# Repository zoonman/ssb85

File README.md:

# ssb85
My work-in-progress hamradio transceiver.

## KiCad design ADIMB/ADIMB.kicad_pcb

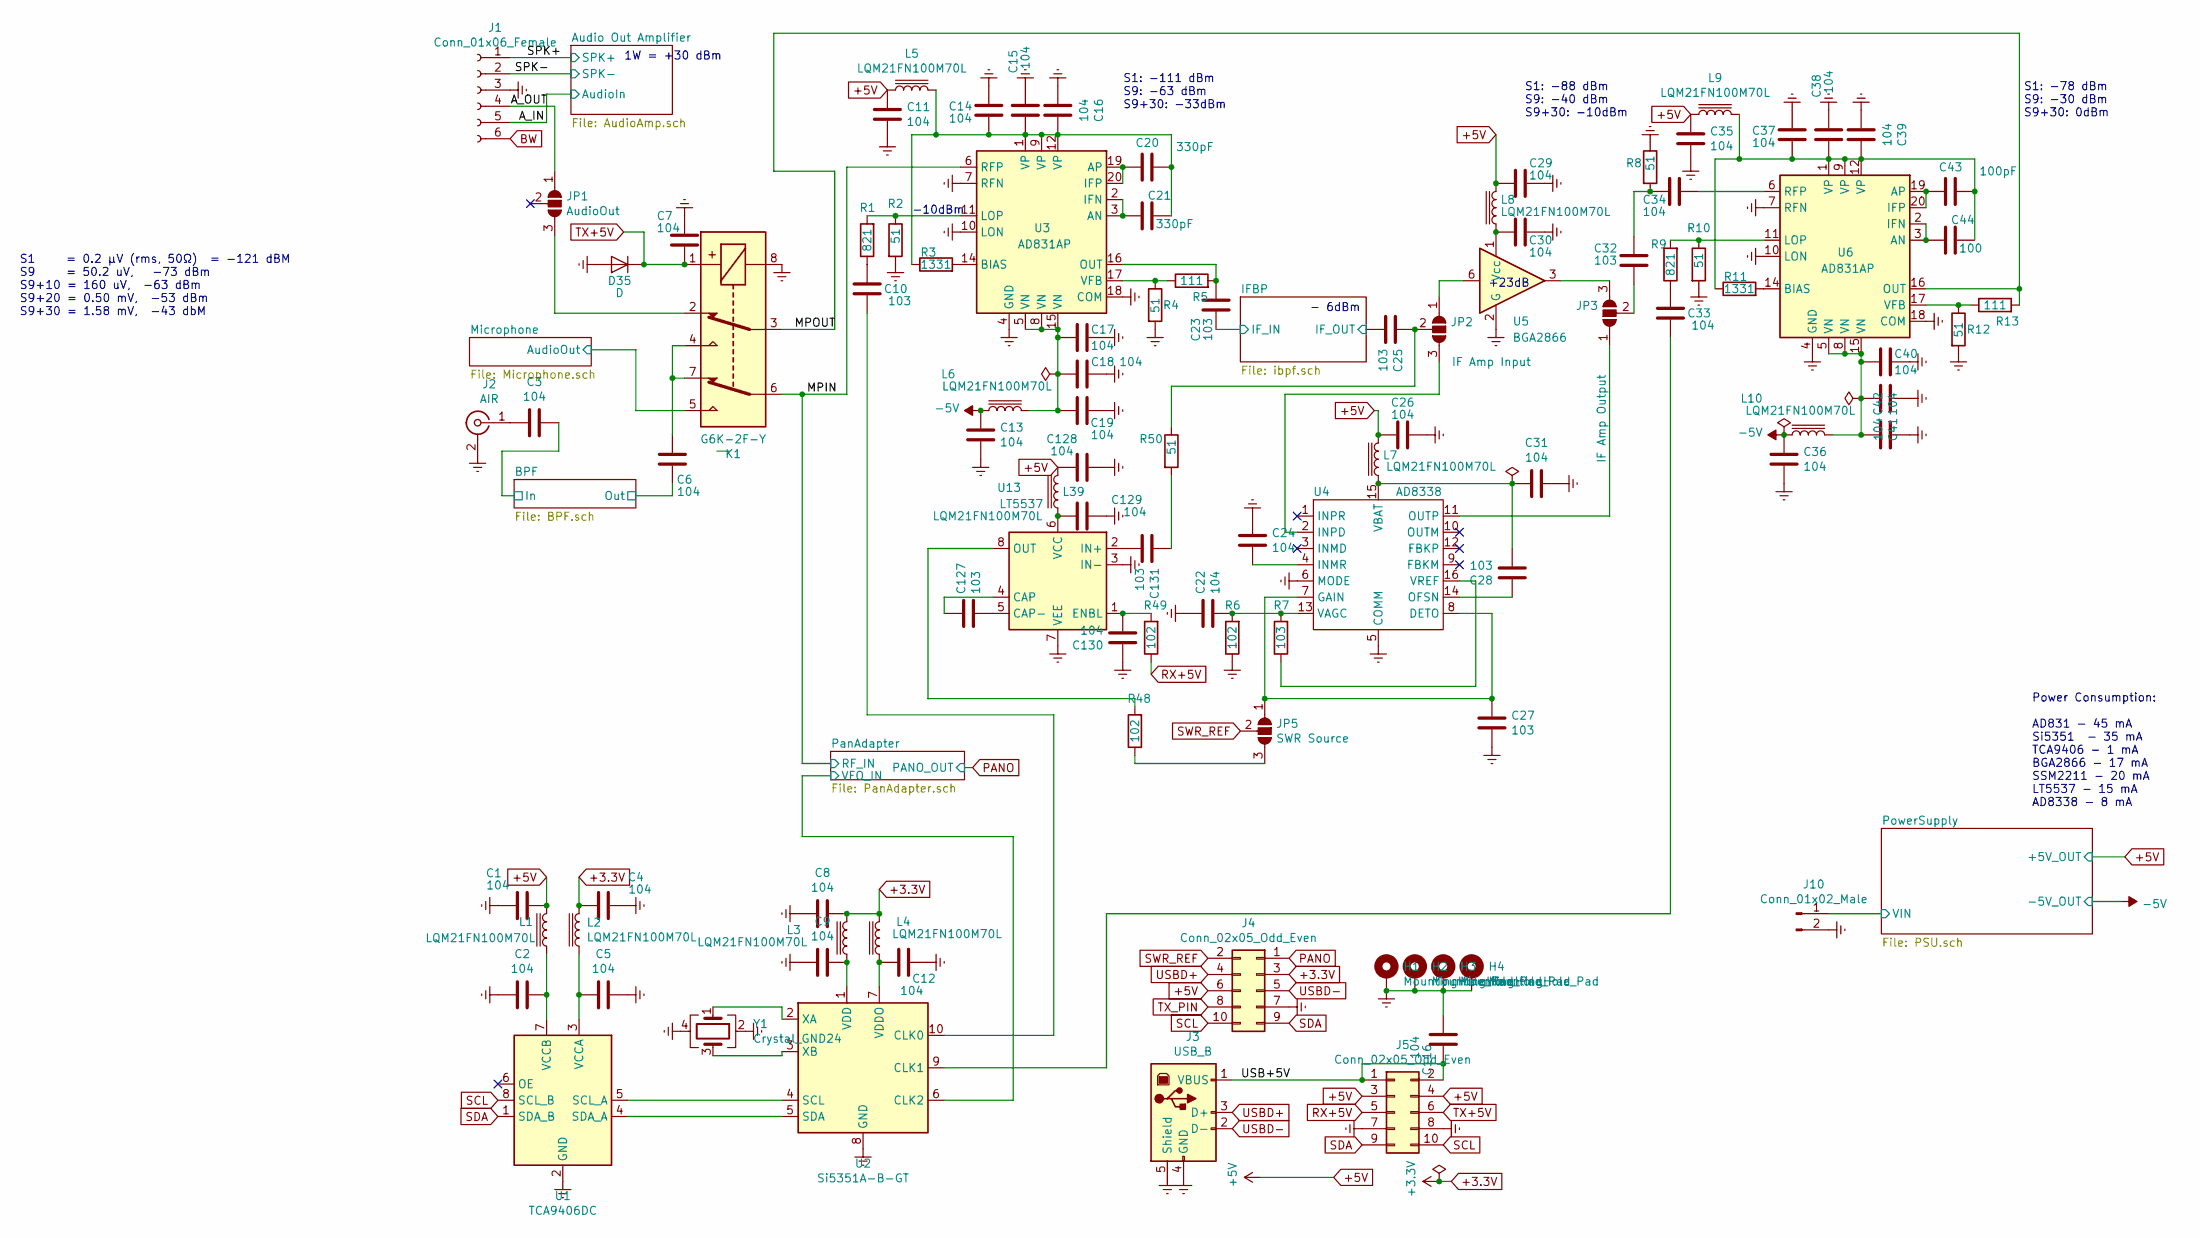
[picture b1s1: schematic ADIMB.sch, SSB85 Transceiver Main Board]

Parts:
C1, C2, C3, C4, C5, C6, C7, C8, C9, C11, C12, C13, C14, C15, C16, C17, C18, C19, C22, C24, C26, C29, C30, C31, C33, C34, C35, C36, C37, C38, C39, C40, C41, C42, C116, C128, C129, C130: 104; C_0805_2012Metric
C10, C23, C25, C27, C28, C32, C127, C131: 103; C_0805_2012Metric
C20, C21: 330pF; C_0805_2012Metric
C43: 100pF; C_0805_2012Metric
C44: 100; C_0805_2012Metric
D35: D; D_SOD-123
H1, H2, H3, H4: MountingHole_Pad; MountingHole_3.2mm_M3_Pad_Via
J1: Conn_01x06_Female; PinSocket_1x06_P2.54mm_Horizontal
J2: AIR; SMA_Amphenol_901-144_Vertical
J3: USB_B; USB_B_OST_USB-B1HSxx_Horizontal
J4: Conn_02x05_Odd_Even; PinSocket_2x05_P2.54mm_Horizontal
J5: Conn_02x05_Odd_Even; PinSocket_2x05_P2.54mm_Vertical
J10: Conn_01x02_Male; PinHeader_1x02_P2.54mm_Vertical
JP1: AudioOut; SolderJumper-3_P1.3mm_Open_RoundedPad1.0x1.5mm
JP2: IF Amp Input; SolderJumper-3_P1.3mm_Open_RoundedPad1.0x1.5mm
JP3: IF Amp Output; SolderJumper-3_P1.3mm_Open_RoundedPad1.0x1.5mm
JP5: SWR Source; SolderJumper-3_P1.3mm_Open_RoundedPad1.0x1.5mm
K1: G6K-2F-Y; Relay_DPDT_Omron_G6K-2F-Y
L1, L2, L3, L4, L5, L6, L7, L8, L9, L10, L39: LQM21FN100M70L; L_0805_2012Metric
R1, R9: 821; R_0805_2012Metric
R2, R4, R8, R10, R12, R50: 51; R_0805_2012Metric
R3, R11: 1331; R_0805_2012Metric
R5, R13: 111; R_0805_2012Metric
R6, R48, R49: 102; R_0805_2012Metric
R7: 103; R_0805_2012Metric
U1: TCA9406DC; VSSOP-8_2.3x2mm_P0.5mm
U2: Si5351A-B-GT; MSOP-10_3x3mm_P0.5mm
U3, U6: AD831AP; PLCC-20
U4: AD8338; LFCSP-16-1EP_3x3mm_P0.5mm_EP1.7x1.7mm
U5: BGA2866; SOT-363_SC-70-6
U13: LT5537; DFN-8-1EP_2x3mm_P0.5mm_EP0.61x2.2mm
Y1: Crystal_GND24; Crystal_SMD_Abracon_ABM8G-4Pin_3.2x2.5mm

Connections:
+3.3V: C4.2, C8.1, J4.3, L2.2, L3.2, L4.2
+5V: C1.1, C11.1, C26.2, C29.2, C35.1, C128.2, J4.6, J5.3, J5.4, L1.2, L5.1, L7.2, L8.2, L9.1, L39.2; also elsewhere on the board
-5V: C13.1, C36.1, L6.1, L10.1; also elsewhere on the board
/A_IN: J1.5; also elsewhere on the board
/A_OUT: J1.4, JP1.1 (A)
/BPF/In: C3.1; also elsewhere on the board
/BPF/Out: C6.1; also elsewhere on the board
/IFBP/IF_IN: C23.1; also elsewhere on the board
/IFBP/IF_OUT: C25.2; also elsewhere on the board
/MPIN: K1.6, U3.6 (RFP); also elsewhere on the board
/MPOUT: K1.3, R13.2, U6.16 (OUT)
/Microphone/AudioOut: K1.5; also elsewhere on the board
/PanAdapter/VFO_IN: U2.6 (CLK2); also elsewhere on the board
/PowerSupply/VIN: J10.1; also elsewhere on the board
/SPK+: J1.1; also elsewhere on the board
/SPK-: J1.2; also elsewhere on the board
/USB+5V: C116.1, J3.1 (VBUS), J5.1, J5.2
BW: J1.6; also elsewhere on the board
Earth: C1.2, C2.2, C4.1, C5.1, C7.1, C8.2, C9.2, C11.2, C12.1, C13.2, C14.2, C15.2, C16.2, C17.1, C18.1, C19.2, C22.1, C24.1, C26.1, C27.2, C29.1, C30.1, C31.1, C35.2, C36.2, C37.2, C38.2, C39.2, C40.1, C41.1, C42.2, C116.2, C128.1, C129.1, C130.1, D35.2 (A), H1.1, H2.1, H3.1, H4.1, J1.3, J2.2 (Ext), J3.4 (GND), J3.5 (Shield), J4.7, J5.7, J5.8, J10.2, K1.8, R2.2, R4.2, R6.1, R8.1, R10.2, R12.2, U1.2 (GND), U2.8 (GND), U3.4 (GND), U3.7 (RFN), U3.10 (LON), U3.13 (GND), U3.18 (COM), U4.5 (COMM), U4.6 (MODE), U4.17 (EPAD), U5.2 (G), U5.4 (G), U5.5 (G), U6.4 (GND), U6.7 (RFN), U6.10 (LON), U6.13 (GND), U6.18 (COM), U13.3 (IN-), U13.7 (VEE), U13.9 (PAD), Y1.2, Y1.4; also elsewhere on the board
unnamed: C2.1, L1.1, U1.7 (VCCB)
unnamed: C3.2, J2.1 (In)
unnamed: C5.2, L2.1, U1.3 (VCCA)
unnamed: C6.2, K1.4, K1.7
unnamed: C9.1, L3.1, U2.1 (VDD)
unnamed: C10.1, R1.1
unnamed: C10.2, U2.10 (CLK0)
unnamed: C12.2, L4.1, U2.7 (VDDO)
unnamed: C14.1, C15.1, C16.1, C20.1, C21.1, L5.2, R3.1, U3.1 (VP), U3.9 (VP), U3.12 (VP)
unnamed: C17.2, C18.2, C19.1, L6.2, U3.5 (VN), U3.8 (VN), U3.15 (VN)
unnamed: C20.2, U3.19 (AP), U3.20 (IFP)
unnamed: C21.2, U3.2 (IFN), U3.3 (AN)
unnamed: C22.2, R6.2, R7.2, U4.13 (VAGC)
unnamed: C23.2, R5.2, U3.16 (OUT)
unnamed: C24.2, U4.4 (INMR)
unnamed: C25.1, JP2.2 (C), R50.1
unnamed: C27.1, JP5.1 (A), U4.7 (GAIN), U4.8 (DETO)
unnamed: C28.1, U4.14 (OFSN)
unnamed: C28.2, C31.2, L7.1, U4.15 (VBAT)
unnamed: C30.2, L8.1, U5.1 (Vcc)
unnamed: C32.1, JP3.2 (C)
unnamed: C32.2, C34.2, R8.2
unnamed: C33.1, R9.1
unnamed: C33.2, U2.9 (CLK1)
unnamed: C34.1, U6.6 (RFP)
unnamed: C37.1, C38.1, C39.1, C43.1, C44.1, L9.2, R11.1, U6.1 (VP), U6.9 (VP), U6.12 (VP)
unnamed: C40.2, C41.2, C42.1, L10.2, U6.5 (VN), U6.8 (VN), U6.15 (VN)
unnamed: C43.2, U6.19 (AP), U6.20 (IFP)
unnamed: C44.2, U6.2 (IFN), U6.3 (AN)
unnamed: C127.1, U13.4 (CAP)
unnamed: C127.2, U13.5 (CAP-)
unnamed: C129.2, L39.1, U13.6 (VCC)
unnamed: C130.2, R49.2, U13.1 (ENBL)
unnamed: C131.1, R50.2
unnamed: C131.2, U13.2 (IN+)
unnamed: JP1.3 (B), K1.2
unnamed: JP2.1 (A), U5.6
unnamed: JP2.3 (B), U4.2 (INPD)
unnamed: JP3.1 (A), U4.11 (OUTP)
unnamed: JP3.3 (B), U5.3
unnamed: JP5.3 (B), R48.1
unnamed: R1.2, R2.1, U3.11 (LOP)
unnamed: R3.2, U3.14 (BIAS)
unnamed: R4.1, R5.1, U3.17 (VFB)
unnamed: R7.1, U4.16 (VREF)
unnamed: R9.2, R10.1, U6.11 (LOP)
unnamed: R11.2, U6.14 (BIAS)
unnamed: R12.1, R13.1, U6.17 (VFB)
unnamed: R48.2, U13.8 (OUT)
unnamed: U1.4 (SDA_A), U2.5 (SDA)
unnamed: U1.5 (SCL_A), U2.4 (SCL)
unnamed: U2.2 (XA), Y1.1
unnamed: U2.3 (XB), Y1.3
PANO: J4.1; also elsewhere on the board
RX+5V: J5.5, R49.1; also elsewhere on the board
SCL: J4.10, J5.10, U1.8 (SCL_B); also elsewhere on the board
SDA: J4.9, J5.9, U1.1 (SDA_B); also elsewhere on the board
SWR_REF: J4.2, JP5.2 (C)
TX+5V: C7.2, D35.1 (K), J5.6, K1.1; also elsewhere on the board
TX_PIN: J4.8; also elsewhere on the board
USBD+: J3.3 (D+), J4.4
USBD-: J3.2 (D-), J4.5

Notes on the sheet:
S1 = 0.2 μV (rms, 50Ω) = -121 dBM S9 = 50.2 uV, -73 dBm S9+10 = 160 uV, -63 dBm S9+20 = 0.50 mV, -53 dBm S9+30 = 1.58 mV, -43 dbM
1W = +30 dBm
S1: -111 dBm S9: -63 dBm S9+30: -33dBm
-10dBm
- 6dBm
+23dB
S1: -88 dBm S9: -40 dBm S9+30: -10dBm
S1: -78 dBm S9: -30 dBm S9+30: 0dBm
Power Consumption: AD831 - 45 mA Si5351 - 35 mA TCA9406 - 1 mA BGA2866 - 17 mA SSM2211 - 20 mA LT5537 - 15 mA AD8338 - 8 mA

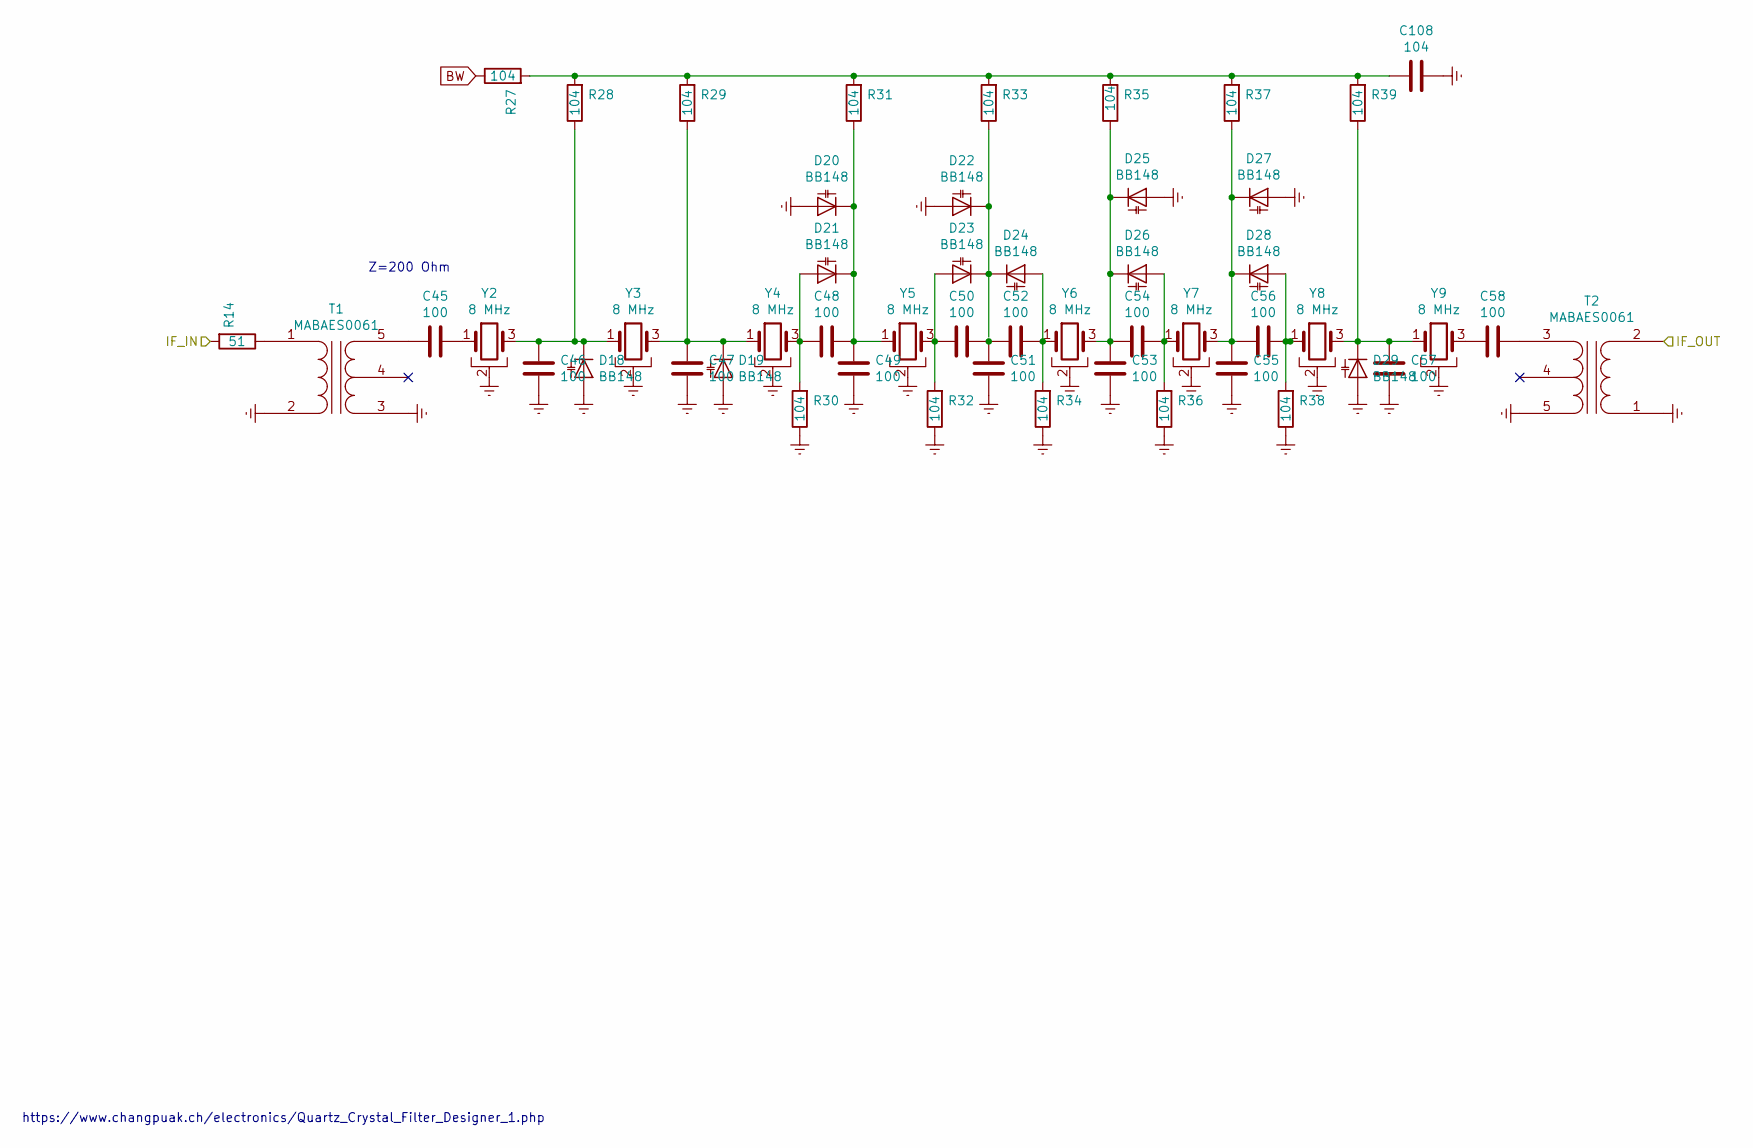
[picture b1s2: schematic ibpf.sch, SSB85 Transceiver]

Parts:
C45, C46, C47, C48, C49, C50, C51, C52, C53, C54, C55, C56, C57, C58: 100; C_0805_2012Metric
C108: 104; C_0805_2012Metric
D18: BB148; D_SOD-323
D19, D20, D21, D22, D23, D24, D25, D26, D27, D28, D29: BB148; D_SOD-323_HandSoldering
R14: 51; R_0805_2012Metric
R27, R28, R29, R30, R31, R32, R33, R34, R35, R36, R37, R38, R39: 104; R_0805_2012Metric
T1, T2: MABAES0061; Transformer_MACOM_SM-22
Y2, Y3, Y4, Y5, Y6, Y7, Y8, Y9: 8 MHz; Crystal_HC49-U-3Pin_Vertical

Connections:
/IFBP/IF_IN: R14.2; also elsewhere on the board
/IFBP/IF_OUT: T2.2 (AB); also elsewhere on the board
BW: R27.1; also elsewhere on the board
Earth: C46.1, C47.1, C49.1, C51.1, C53.1, C55.1, C57.1, C108.1, D18.2 (A), D19.2 (A), D20.2 (A), D22.2 (A), D25.2 (A), D27.2 (A), D29.2 (A), R30.1, R32.1, R34.1, R36.1, R38.1, T1.2 (AB), T1.3 (SA), T2.1 (AA), T2.5 (SB), Y2.2, Y3.2, Y4.2, Y5.2, Y6.2, Y7.2, Y8.2, Y9.2; also elsewhere on the board
unnamed: C45.1, Y2.1
unnamed: C45.2, T1.5 (SB)
unnamed: C46.2, D18.1 (K), R28.1, Y2.3, Y3.1
unnamed: C47.2, D19.1 (K), R29.1, Y3.3, Y4.1
unnamed: C48.1, C49.2, D20.1 (K), D21.1 (K), R31.1, Y5.1
unnamed: C48.2, D21.2 (A), R30.2, Y4.3
unnamed: C50.1, C51.2, C52.2
unnamed: C50.2, D23.2 (A), R32.2, Y5.3
unnamed: C52.1, D24.2 (A), R34.2, Y6.1
unnamed: C53.2, C54.2, D25.1 (K), D26.1 (K), R35.1, Y6.3
unnamed: C54.1, D26.2 (A), R36.2, Y7.1
unnamed: C55.2, C56.2, D27.1 (K), D28.1 (K), R37.1, Y7.3
unnamed: C56.1, D28.2 (A), R38.2, Y8.1
unnamed: C57.2, D29.1 (K), R39.1, Y8.3, Y9.1
unnamed: C58.1, T2.3 (SA)
unnamed: C58.2, Y9.3
unnamed: C108.2, R27.2, R28.2, R29.2, R31.2, R33.2, R35.2, R37.2, R39.2
unnamed: D22.1 (K), D23.1 (K), D24.1 (K), R33.1
unnamed: R14.1, T1.1 (AA)

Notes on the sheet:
Z=200 Ohm
https://www.changpuak.ch/electronics/Quartz_Crystal_Filter_Designer_1.php

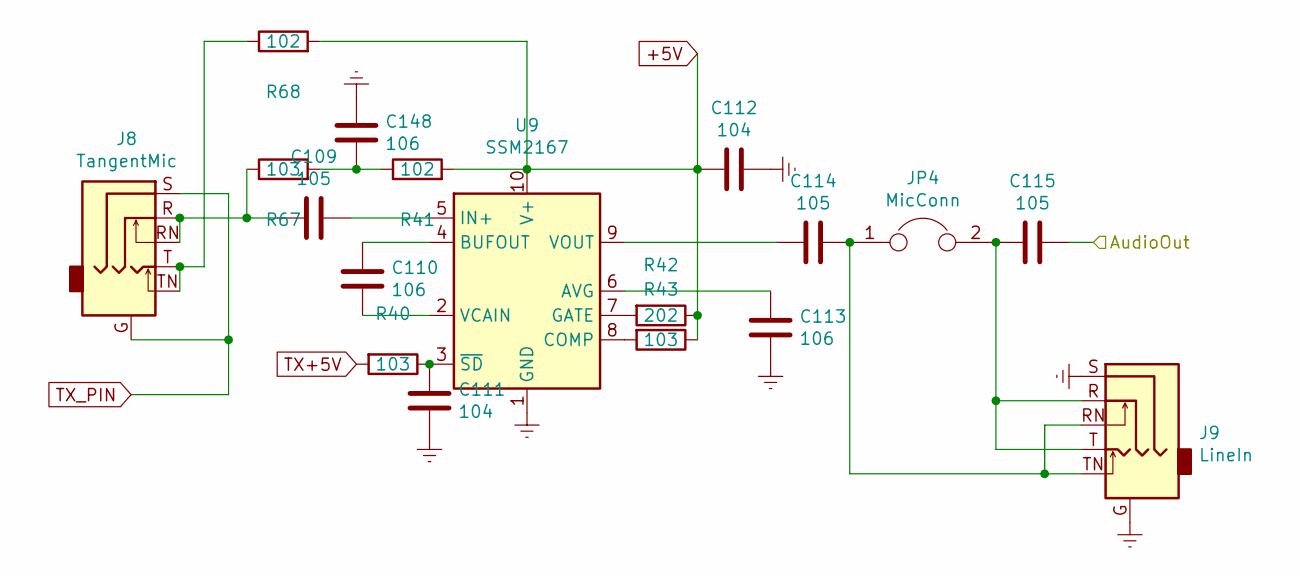
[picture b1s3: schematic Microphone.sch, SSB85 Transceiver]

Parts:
C109, C114, C115: 105; C_0805_2012Metric
C110, C113, C148: 106; C_0805_2012Metric
C111, C112: 104; C_0805_2012Metric
J8: TangentMic; Jack_3.5mm_PJ342_Horizontal2
J9: LineIn; Jack_3.5mm_PJ342_Horizontal2
JP4: MicConn; SolderJumper-2_P1.3mm_Open_RoundedPad1.0x1.5mm
R40, R43, R67: 103; R_0805_2012Metric
R41, R68: 102; R_0805_2012Metric
R42: 202; R_0805_2012Metric
U9: SSM2167; MSOP-10_3x3mm_P0.5mm

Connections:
+5V: C112.1, R41.2, R42.1, R43.1, R68.2, U9.10 (V+); also elsewhere on the board
/Microphone/AudioOut: C115.1; also elsewhere on the board
Earth: C111.1, C112.2, C113.2, C148.1, J9.G, J9.S, U9.1 (GND); also elsewhere on the board
unnamed: C109.1, U9.5 (IN+)
unnamed: C109.2, J8.R, J8.RN, R67.1
unnamed: C110.1, U9.4 (BUFOUT)
unnamed: C110.2, U9.2 (VCAIN)
unnamed: C111.2, R40.1, U9.3 (~SD)
unnamed: C113.1, U9.6 (AVG)
unnamed: C114.1, J9.RN, J9.TN, JP4.1
unnamed: C114.2, U9.9 (VOUT)
unnamed: C115.2, J9.R, J9.T, JP4.2
unnamed: C148.2, R41.1, R67.2
unnamed: J8.T, J8.TN, R68.1
unnamed: R42.2, U9.7 (GATE)
unnamed: R43.2, U9.8 (COMP)
TX+5V: R40.2; also elsewhere on the board
TX_PIN: J8.G, J8.S; also elsewhere on the board

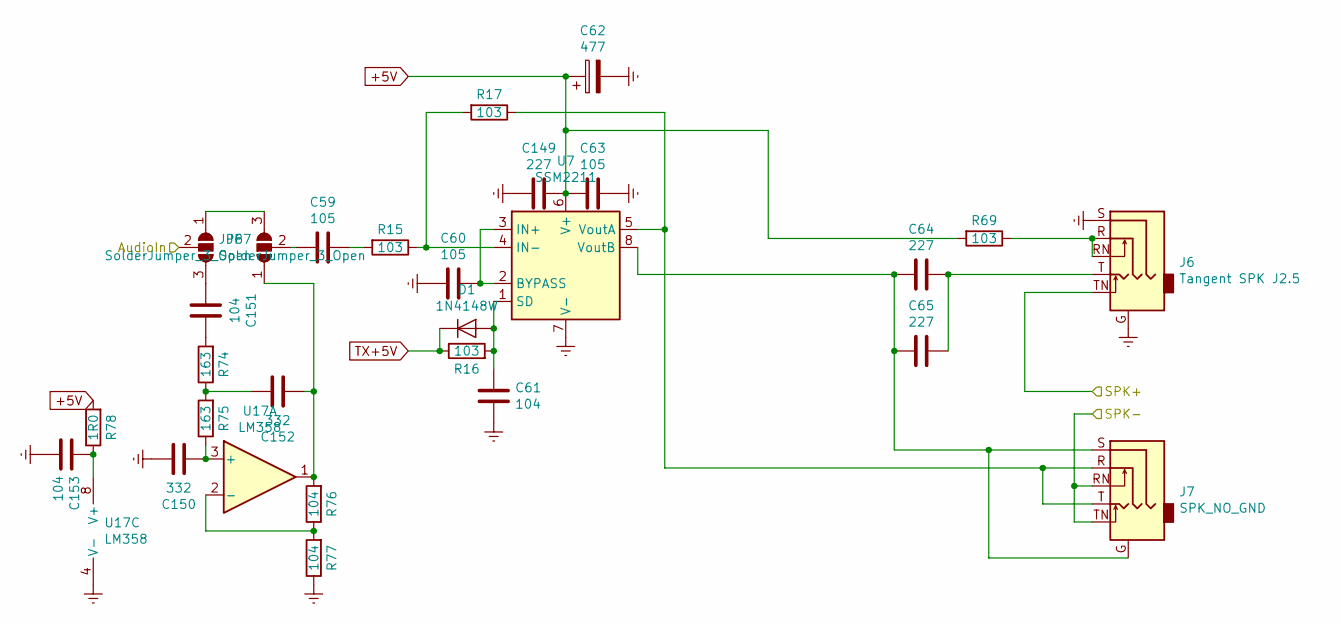
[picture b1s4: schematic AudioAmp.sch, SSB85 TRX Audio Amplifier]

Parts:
C59, C60, C63: 105; C_0805_2012Metric
C61, C151, C153: 104; C_0805_2012Metric
C62: 477; CP_Elec_6.3x7.7
C64, C65, C149: 227; C_1210_3225Metric
C150, C152: 332; C_0805_2012Metric
D1: 1N4148W; D_SOD-123
J6: Tangent SPK J2.5; Jack_2.5mm_PJ242_6P_12x6.2x4mm_Horizontal
J7: SPK_NO_GND; Jack_3.5mm_PJ342_Horizontal2
JP6, JP7: SolderJumper_3_Open; SolderJumper-3_P1.3mm_Open_RoundedPad1.0x1.5mm
R15, R16, R17, R69: 103; R_0805_2012Metric
R74, R75: 163; R_0805_2012Metric
R76, R77: 104; R_0805_2012Metric
R78: 1R0; R_0805_2012Metric
U7: SSM2211; SOIC-8-1EP_3.9x4.9mm_P1.27mm_EP2.29x3mm
U17: LM358; SOIC-8_3.9x4.9mm_P1.27mm

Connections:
+5V: C62.1, C63.2, C149.1, R69.2, R78.2, U7.6 (V+); also elsewhere on the board
/A_IN: JP6.2 (C); also elsewhere on the board
/SPK+: J6.TN; also elsewhere on the board
/SPK-: J7.RN, J7.TN; also elsewhere on the board
Earth: C60.2, C61.1, C62.2, C63.1, C149.2, C150.1, C153.1, J6.G, J6.S, R77.1, U7.7 (V-), U7.9 (V-), U17.4 (V-); also elsewhere on the board
unnamed: C59.1, R15.2
unnamed: C59.2, JP7.2 (C)
unnamed: C60.1, U7.2 (BYPASS), U7.3 (IN+)
unnamed: C61.2, D1.2 (A), R16.2, U7.1 (SD)
unnamed: C64.1, C65.1, J6.T
unnamed: C64.2, C65.2, J7.G, J7.S, U7.8 (VoutB)
unnamed: C150.2, R75.1, U17.3 (+)
unnamed: C151.1, R74.2
unnamed: C151.2, JP6.3 (B)
unnamed: C152.1, R74.1, R75.2
unnamed: C152.2, JP7.1 (A), R76.2, U17.1
unnamed: C153.2, R78.1, U17.8 (V+)
unnamed: J6.R, J6.RN, R69.1
unnamed: J7.R, J7.T, R17.1, U7.5 (VoutA)
unnamed: JP6.1 (A), JP7.3 (B)
unnamed: R15.1, R17.2, U7.4 (IN-)
unnamed: R76.1, R77.2, U17.2 (-)
TX+5V: D1.1 (K), R16.1; also elsewhere on the board

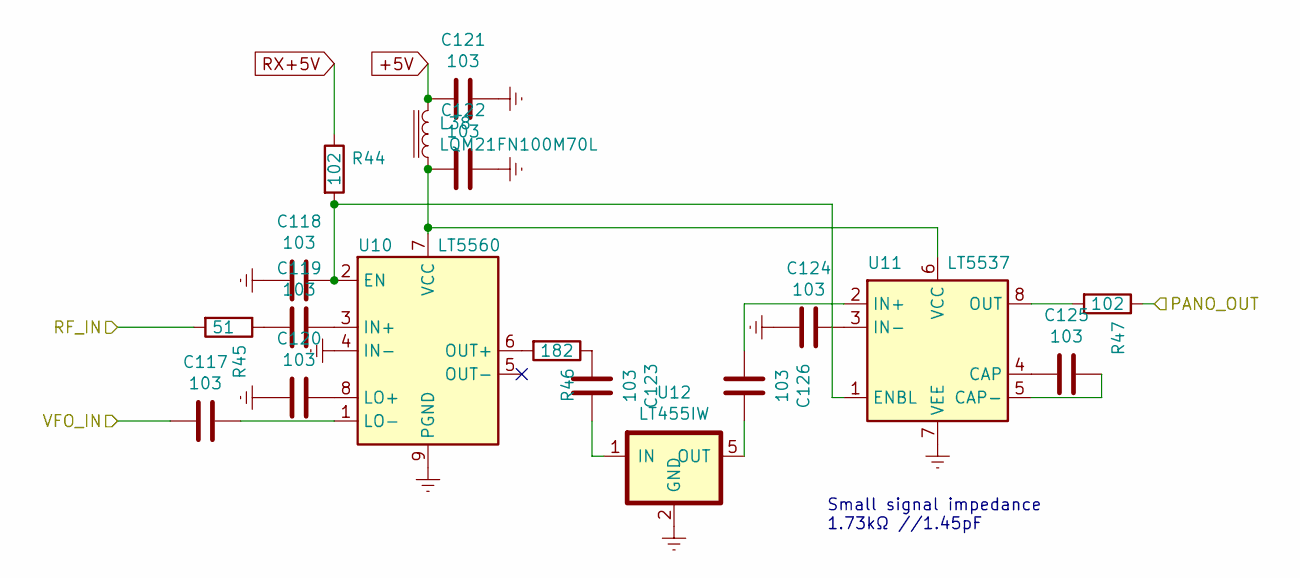
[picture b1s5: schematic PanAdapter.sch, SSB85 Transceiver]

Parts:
C117, C118, C119, C120, C121, C122, C123, C124, C125, C126: 103; C_0805_2012Metric
L38: LQM21FN100M70L; L_0805_2012Metric
R44, R47: 102; R_0805_2012Metric
R45: 51; R_0805_2012Metric
R46: 182; R_0805_2012Metric
U10: LT5560; DFN-8-1EP_3x3mm_P0.5mm_EP1.66x2.38mm
U11: LT5537; DFN-8-1EP_2x3mm_P0.5mm_EP0.61x2.2mm
U12: LT455IW; Filter-LT450-455-11x7

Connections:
+5V: C121.2, L38.2; also elsewhere on the board
/MPIN: R45.2; also elsewhere on the board
/PanAdapter/VFO_IN: C117.2; also elsewhere on the board
Earth: C118.2, C120.2, C121.1, C122.1, C124.2, U10.4 (IN-), U10.9 (PGND), U11.7 (VEE), U11.9 (PAD), U12.2 (GND), U12.3 (GND), U12.4 (GND); also elsewhere on the board
unnamed: C117.1, U10.1 (LO-)
unnamed: C118.1, R44.2, U10.2 (EN), U11.1 (ENBL)
unnamed: C119.1, U10.3 (IN+)
unnamed: C119.2, R45.1
unnamed: C120.1, U10.8 (LO+)
unnamed: C122.2, L38.1, U10.7 (VCC), U11.6 (VCC)
unnamed: C123.1, U12.1 (IN)
unnamed: C123.2, R46.1
unnamed: C124.1, U11.3 (IN-)
unnamed: C125.1, U11.5 (CAP-)
unnamed: C125.2, U11.4 (CAP)
unnamed: C126.1, U12.5 (OUT)
unnamed: C126.2, U11.2 (IN+)
unnamed: R46.2, U10.6 (OUT+)
unnamed: R47.2, U11.8 (OUT)
PANO: R47.1; also elsewhere on the board
RX+5V: R44.1; also elsewhere on the board

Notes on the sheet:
Small signal impedance 1.73kΩ //1.45pF

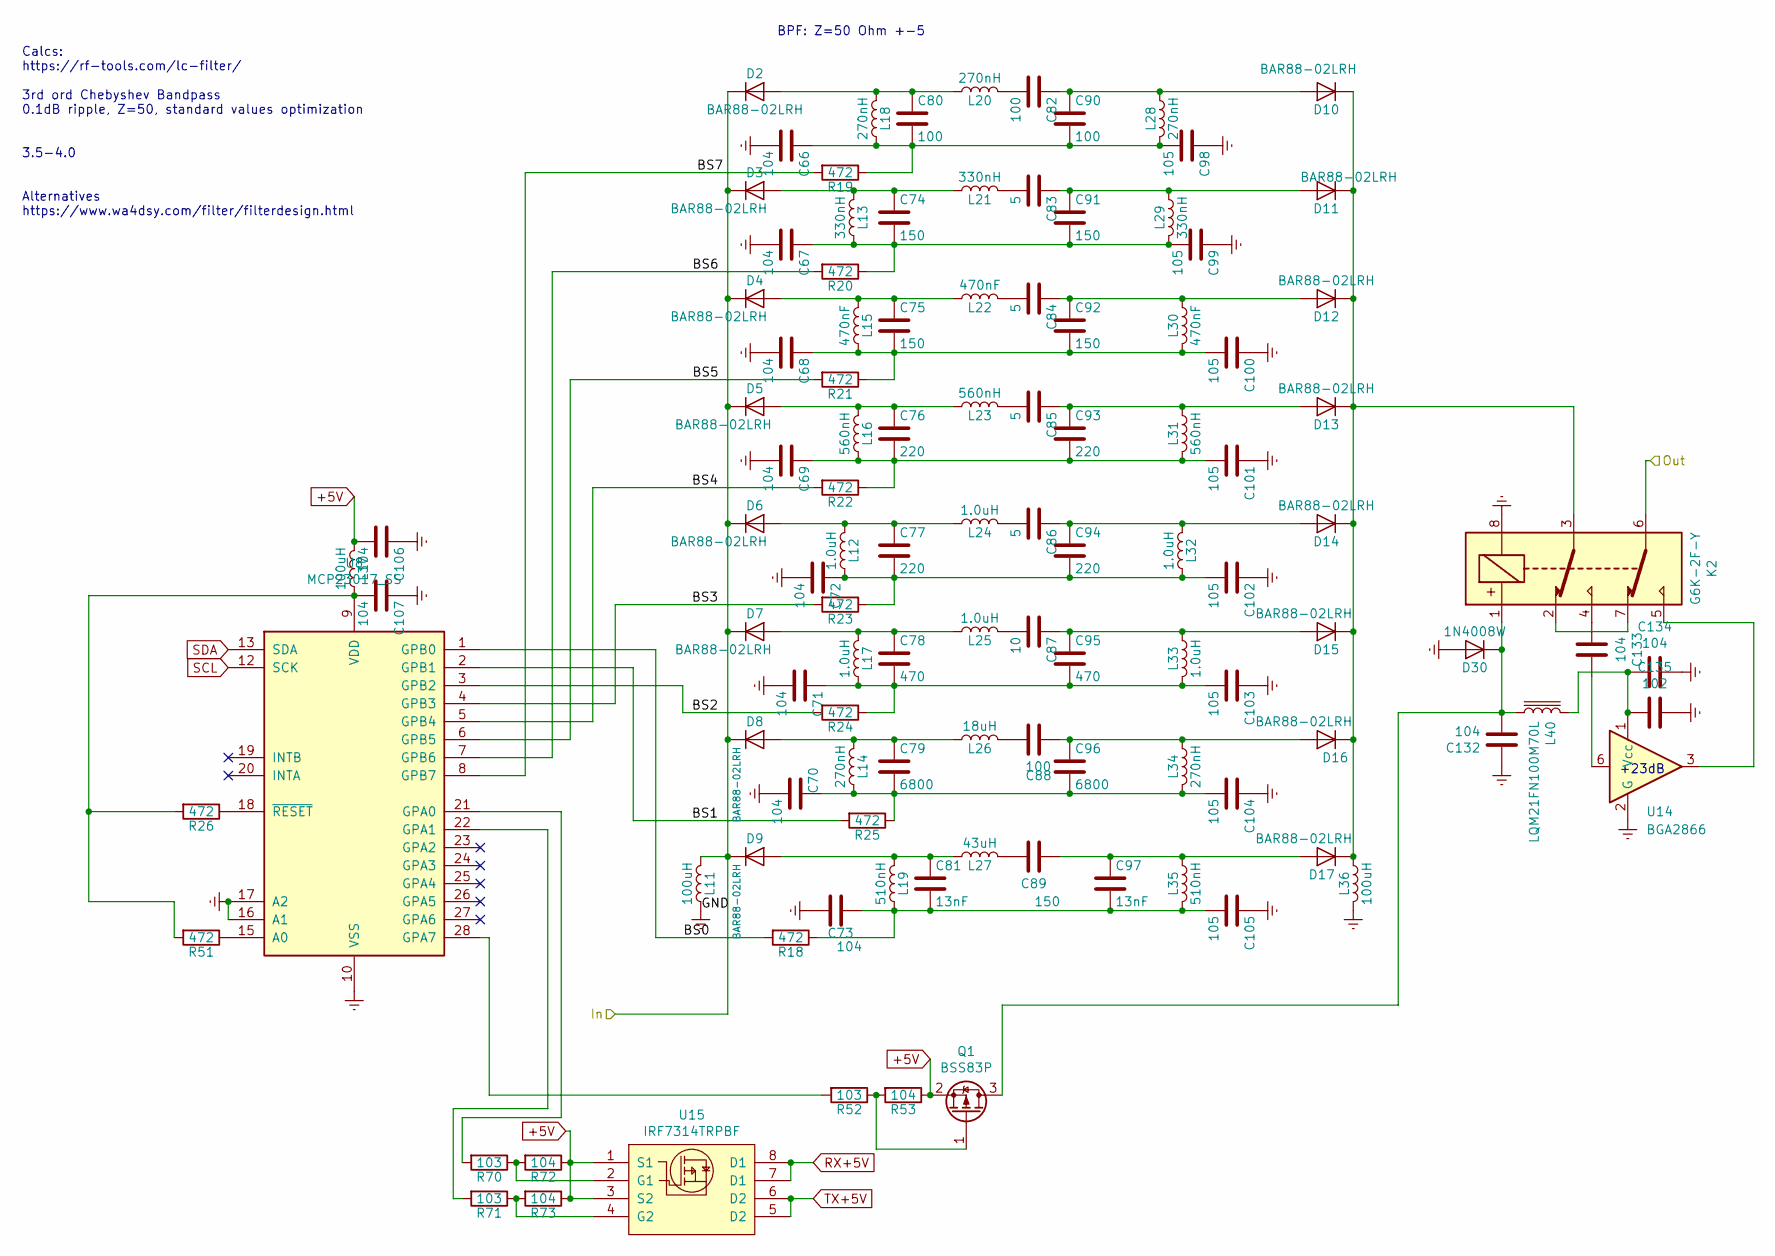
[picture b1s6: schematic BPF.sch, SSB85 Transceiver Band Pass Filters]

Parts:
C66, C67, C68, C69, C70, C71, C72, C73, C106, C107, C132, C133, C134: 104; C_0805_2012Metric
C74, C75, C89, C91, C92: 150; C_0805_2012Metric
C76, C77, C93, C94: 220; C_0805_2012Metric
C78, C95: 470; C_0805_2012Metric
C79, C96: 6800; C_0805_2012Metric
C80, C82, C88, C90: 100; C_0805_2012Metric
C81, C97: 13nF; C_0805_2012Metric
C83, C84, C85, C86: 5; C_0805_2012Metric
C87: 10; C_0805_2012Metric
C98, C99, C100, C101, C102, C103, C104, C105: 105; C_0805_2012Metric
C135: 102; C_0805_2012Metric
D2, D3, D4, D5, D6, D7, D8, D9, D10, D11, D12, D13, D14, D15, D16, D17: BAR88-02LRH; D_0402_1005Metric
D30: 1N4008W; D_SOD-123
K2: G6K-2F-Y; Relay_DPDT_Omron_G6K-2F-Y
L11, L36, L37: 100uH; L_0805_2012Metric
L12, L17, L24, L25, L32, L33: 1.0uH; L_0805_2012Metric
L13, L21, L29: 330nH; L_0805_2012Metric
L14, L18, L20, L28, L34: 270nH; L_0805_2012Metric
L15, L22, L30: 470nF; L_0805_2012Metric
L16, L23, L31: 560nH; L_0805_2012Metric
L19, L35: 510nH; L_0805_2012Metric
L26: 18uH; L_0805_2012Metric
L27: 43uH; L_0805_2012Metric
L40: LQM21FN100M70L; L_0805_2012Metric
Q1: BSS83P; SOT-23
R18, R19, R20, R21, R22, R23, R24, R25, R26, R51: 472; R_0805_2012Metric
R52, R70, R71: 103; R_0805_2012Metric
R53, R72, R73: 104; R_0805_2012Metric
U8: MCP23017_SS; SSOP-28_5.3x10.2mm_P0.65mm
U14: BGA2866; SOT-363_SC-70-6
U15: IRF7314TRPBF; SOIC-8_3.9x4.9mm_P1.27mm

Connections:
+5V: C106.2, L37.1, Q1.2 (S), R53.1, R72.1, R73.1, U15.1 (S1), U15.3 (S2); also elsewhere on the board
/BPF/BS0: R18.2, U8.1 (GPB0)
/BPF/BS1: R25.2, U8.2 (GPB1)
/BPF/BS2: R24.2, U8.3 (GPB2)
/BPF/BS3: R23.2, U8.4 (GPB3)
/BPF/BS4: R22.2, U8.5 (GPB4)
/BPF/BS5: R21.2, U8.6 (GPB5)
/BPF/BS6: R20.2, U8.7 (GPB6)
/BPF/BS7: R19.2, U8.8 (GPB7)
/BPF/In: D2.1 (K), D3.1 (K), D4.1 (K), D5.1 (K), D6.1 (K), D7.1 (K), D8.1 (K), D9.1 (K), L11.1; also elsewhere on the board
/BPF/Out: K2.6; also elsewhere on the board
Earth: C66.2, C67.2, C68.2, C69.2, C70.2, C71.2, C72.2, C73.2, C98.1, C99.1, C100.1, C101.1, C102.1, C103.1, C104.1, C105.1, C106.1, C107.1, C132.1, C134.1, C135.1, D30.2 (A), K2.8, L11.2, L36.2, U8.10 (VSS), U8.16 (A1), U8.17 (A2), U14.2 (G), U14.4 (G), U14.5 (G); also elsewhere on the board
unnamed: C66.1, C80.2, C90.2, C98.2, L18.2, L28.2, R19.1
unnamed: C67.1, C74.2, C91.2, C99.2, L13.2, L29.2, R20.1
unnamed: C74.1, D3.2 (A), L13.1, L21.1
unnamed: C75.1, D4.2 (A), L15.1, L22.2
unnamed: C76.1, D5.2 (A), L16.1, L23.2
unnamed: C77.1, D6.2 (A), L12.1, L24.2
unnamed: C78.1, D7.2 (A), L17.1, L25.2
unnamed: C79.1, D8.2 (A), L14.2, L26.1
unnamed: C80.1, D2.2 (A), L18.1, L20.1
unnamed: C81.1, D9.2 (A), L19.1, L27.2
unnamed: C82.1, C90.1, D10.2 (A), L28.1
unnamed: C82.2, L20.2
unnamed: C83.1, C91.1, D11.2 (A), L29.1
unnamed: C83.2, L21.2
unnamed: C84.1, C92.1, D12.2 (A), L30.1
unnamed: C84.2, L22.1
unnamed: C85.1, C93.1, D13.2 (A), L31.1
unnamed: C85.2, L23.1
unnamed: C86.1, C94.1, D14.2 (A), L32.1
unnamed: C86.2, L24.1
unnamed: C87.1, C95.1, D15.2 (A), L33.1
unnamed: C87.2, L25.1
unnamed: C88.1, C96.1, D16.2 (A), L34.1
unnamed: C88.2, L26.2
unnamed: C89.1, C97.1, D17.2 (A), L35.1
unnamed: C89.2, L27.1
unnamed: C68.1, C75.2, C92.2, C100.2, L15.2, L30.2, R21.1
unnamed: C69.1, C76.2, C93.2, C101.2, L16.2, L31.2, R22.1
unnamed: C72.1, C77.2, C94.2, C102.2, L12.2, L32.2, R23.1
unnamed: C71.1, C78.2, C95.2, C103.2, L17.2, L33.2, R24.1
unnamed: C70.1, C79.2, C96.2, C104.2, L14.1, L34.2, R25.1
unnamed: C73.1, C81.2, C97.2, C105.2, L19.2, L35.2, R18.1
unnamed: C107.2, L37.2, R26.2, R51.2, U8.9 (VDD)
unnamed: C132.2, D30.1 (K), K2.1, L40.1, Q1.3 (D)
unnamed: C133.1, U14.6
unnamed: C133.2, K2.4
unnamed: C134.2, C135.2, L40.2, U14.1 (Vcc)
unnamed: D10.1 (K), D11.1 (K), D12.1 (K), D13.1 (K), D14.1 (K), D15.1 (K), D16.1 (K), D17.1 (K), K2.3, L36.1
unnamed: K2.2, K2.7
unnamed: K2.5, U14.3
unnamed: Q1.1 (G), R52.1, R53.2
unnamed: R26.1, U8.18 (~RESET~)
unnamed: R51.1, U8.15 (A0)
unnamed: R52.2, U8.28 (GPA7)
unnamed: R70.1, R72.2, U15.2 (G1)
unnamed: R70.2, U8.21 (GPA0)
unnamed: R71.1, R73.2, U15.4 (G2)
unnamed: R71.2, U8.22 (GPA1)
RX+5V: U15.7 (D1), U15.8 (D1); also elsewhere on the board
SCL: U8.12 (SCK); also elsewhere on the board
SDA: U8.13 (SDA); also elsewhere on the board
TX+5V: U15.5 (D2), U15.6 (D2); also elsewhere on the board

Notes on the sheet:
BPF: Z=50 Ohm +-5
+23dB
Calcs: https://rf-tools.com/lc-filter/ 3rd ord Chebyshev Bandpass 0.1dB ripple, Z=50, standard values optimization 3.5-4.0 Alternatives https://www.wa4dsy.com/filter/filterdesign.html

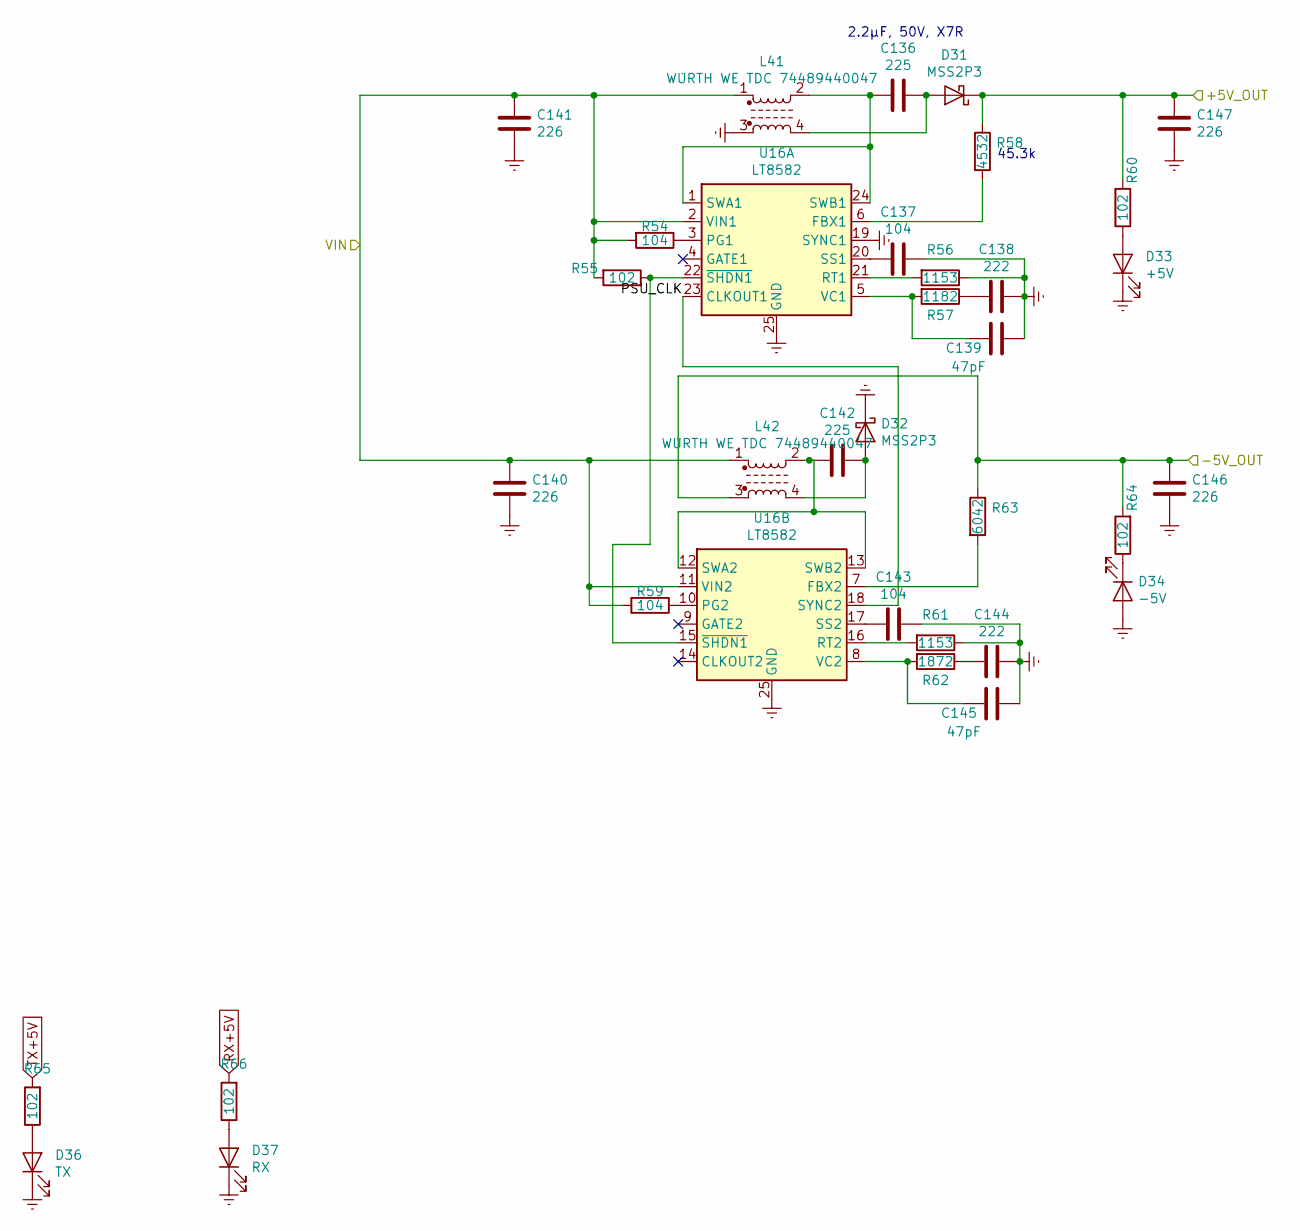
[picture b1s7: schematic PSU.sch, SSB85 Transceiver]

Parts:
C136, C142: 225; C_1206_3216Metric
C137, C143: 104; C_0805_2012Metric
C138, C144: 222; C_0805_2012Metric
C139, C145: 47pF; C_0805_2012Metric
C140, C141, C146, C147: 226; C_1210_3225Metric
D31, D32: MSS2P3; D_PowerDI-123
D33: +5V; D_0603_1608Metric
D34: -5V; D_0603_1608Metric
D36: TX; D_0603_1608Metric
D37: RX; D_0603_1608Metric
L41, L42: WÜRTH WE TDC 74489440047; WE-TDC-8038
R54, R59: 104; R_0805_2012Metric
R55, R60, R64, R65, R66: 102; R_0805_2012Metric
R56, R61: 1153; R_0805_2012Metric
R57: 1182; R_0805_2012Metric
R58: 4532; R_0805_2012Metric
R62: 1872; R_0805_2012Metric
R63: 6042; R_0805_2012Metric
U16: LT8582; DFN-24-1EP_4x7mm_P0.5mm_EP2.64x6.44mm

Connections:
+5V: C147.2, D31.1 (K), R58.1, R60.2; also elsewhere on the board
-5V: C146.2, L42.3, R63.1, R64.2; also elsewhere on the board
/PowerSupply/PSU_CLK: U16.18 (SYNC2), U16.23 (CLKOUT1)
/PowerSupply/VIN: C140.2, C141.2, L41.1, L42.1, R54.2, R55.2, R59.2, U16.2 (VIN1), U16.11 (VIN2); also elsewhere on the board
Earth: C137.2, C138.2, C139.2, C140.1, C141.1, C143.2, C144.2, C145.2, C146.1, C147.1, D32.1 (K), D33.1 (K), D34.2 (A), D36.1 (K), D37.1 (K), L41.3, R56.1, R61.1, U16.19 (SYNC1), U16.25 (GND); also elsewhere on the board
unnamed: C136.1, D31.2 (A), L41.4
unnamed: C136.2, L41.2, U16.1 (SWA1), U16.24 (SWB1)
unnamed: C137.1, U16.20 (SS1)
unnamed: C138.1, R57.1
unnamed: C139.1, R57.2, U16.5 (VC1)
unnamed: C142.1, D32.2 (A), L42.4
unnamed: C142.2, L42.2, U16.12 (SWA2), U16.13 (SWB2)
unnamed: C143.1, U16.17 (SS2)
unnamed: C144.1, R62.1
unnamed: C145.1, R62.2, U16.8 (VC2)
unnamed: D33.2 (A), R60.1
unnamed: D34.1 (K), R64.1
unnamed: D36.2 (A), R65.1
unnamed: D37.2 (A), R66.1
unnamed: R54.1, U16.3 (PG1)
unnamed: R55.1, U16.15 (~SHDN1), U16.22 (~SHDN1)
unnamed: R56.2, U16.21 (RT1)
unnamed: R58.2, U16.6 (FBX1)
unnamed: R59.1, U16.10 (PG2)
unnamed: R61.2, U16.16 (RT2)
unnamed: R63.2, U16.7 (FBX2)
RX+5V: R66.2; also elsewhere on the board
TX+5V: R65.2; also elsewhere on the board

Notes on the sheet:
45.3k
2.2μF, 50V, X7R

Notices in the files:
ADIMB/ADIMB.kicad_pcb:
(c) 2019, Philipp Tkachev
